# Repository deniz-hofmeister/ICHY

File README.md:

# ICHY - 8-Element Microphone Phased Array

## Project Overview
ICHY is a 8-element microphone phased array designed for high-precision audio source localization and beamforming. This document outlines the key design considerations, components, and implementation approach.

## Key Design Elements

### Hardware
- **Microphones**: 8 MEMS microphones with matched frequency response
- **Geometry**: Square array of 4x4 microphones
- **Spacing**: λ/2 spacing to prevent spatial aliasing at target frequencies
- **ADC**: Simultaneous sampling across all channels

### Signal Processing
- **Beamforming Algorithm**: Delay-and-sum with optional adaptive algorithms
- **Calibration**: Inter-microphone calibration methodology
- **Filtering**: Band-pass filtering to focus on frequencies of interest
- **Direction Finding**: MUSIC or SRP-PHAT algorithm implementation

### Software
- **DSP Pipeline**: Real-time processing chain
- **Visualization**: Direction-of-arrival display
- **Interface**: Configuration and monitoring interface
- **Data Storage**: Recording capabilities for post-processing

### Performance Targets
- **Angular Resolution**: <5° at target frequency range
- **Frequency Range**: 1kHz - 8kHz optimal operation
- **Processing Latency**: <50ms for real-time applications

## Data Acquisition Architecture

### Minimal Hardware Configuration for Jetson Processing

#### Essential Hardware Components
- **Microphones**: 8 digital MEMS microphones (I2S/PDM output)
- **Clock Source**: Single master clock with distribution network to ensure phase alignment
- **Audio Codec/Interface**: Audio interface with multi-channel input capabilities
- **Physical Array Structure**: Precise physical positioning framework for microphones
- **Power Conditioning**: Clean power supply with proper isolation

#### Non-Replaceable Hardware Elements
1. **Microphone Transducers**: Physical conversion of sound to electrical signals cannot be done in software
2. **Clock Synchronization Hardware**: Physical timing alignment between microphones (~1μs precision)
3. **Physical Array Geometry**: Precise spatial positioning that affects beamforming accuracy
4. **Signal Conditioning**: Analog filters and buffers to maintain signal integrity
5. **ADC Hardware**: Conversion from analog to digital (integrated in digital MEMS mics)

### Jetson-Based Processing Approach
- **Direct Interfaces**: Utilize Jetson's I2S/SPI interfaces for direct microphone connection where possible
- **Audio Interface Options**:
  1. Direct connection of PDM microphones to Jetson's hardware interfaces
  2. Multi-channel audio codec with TDM output connected to Jetson
  3. USB audio interface with multi-channel capability

### Software-Replaceable Components
- **Digital Filtering**: All filtering can be performed in software on Jetson
- **Beamforming Algorithms**: Implemented entirely in CUDA on Jetson GPU
- **Signal Conditioning**: Digital gain, normalization in software
- **Channel Synchronization**: Fine synchronization adjustments in software
- **Calibration**: Software-based microphone calibration routines
- **Direction Finding**: All direction finding algorithms in CUDA

### Jetson Processing Implementation
- **Nvidia Jetson Advantages**:
  1. **Integrated Solution**: ARM CPU cores + CUDA-capable GPU on single board
  2. **Direct I/O**: Hardware interfaces for connecting to microphone array
  3. **Unified Memory**: Shared memory architecture for efficient CPU-GPU data exchange
  4. **Complete Software Stack**: CUDA libraries for signal processing optimization
  
- **Jetson Signal Processing Pipeline**:
  1. **Data Acquisition**: 
     - Direct digital sampling from microphones via I2S/PDM interfaces
     - DMA transfer to Jetson memory with minimal CPU involvement
  
  2. **Pre-Processing on CPU**:
     - Initial buffering and sample rate conversion if needed
     - Channel synchronization fine-tuning
     - Data preparation for GPU processing
  
  3. **GPU Processing with CUDA**:
     - Batch processing of multi-channel audio data
     - FFT-based operations across all channels in parallel
     - Beamforming coefficients calculation
     - Direction-of-arrival estimation using MUSIC/SRP-PHAT
  
  4. **Real-time Visualization and Output**:
     - Direction finding results visualization
     - Beamformed audio output
     - Optional raw data storage for post-processing

- **Optimized Jetson Implementation**:
  - Use of Jetson-specific optimizations (cuDNN, TensorRT if applicable)
  - Zero-copy memory operations between CPU and GPU when possible
  - Asynchronous processing to maintain real-time performance
  - GPU kernel fusion to minimize data movement

### Power and Thermal Considerations
- **Power Distribution**: Clean, low-noise power supply to each microphone
- **Isolation**: Digital/analog domain isolation to prevent noise coupling
- **Thermal Design**: Heat dissipation strategy for continuous operation

## Design Artifacts

### PCB Design

### Schematic

### 3D View

### Left side of the PCB, right is mirrored

## Next Steps
- Detailed microphone selection and array geometry calculation
- Electronics design and component selection
- DSP algorithm implementation
- Mechanical design and housing
- Software development and user interface
- Testing and calibration methodology

## References
- Key academic papers and resources for phased array design
- Component datasheets and reference implementations

## Developer Guide
- https://docs.nvidia.com/jetson/archives/r36.4/DeveloperGuide/SD/Communications/AudioSetupAndDevelopment.html

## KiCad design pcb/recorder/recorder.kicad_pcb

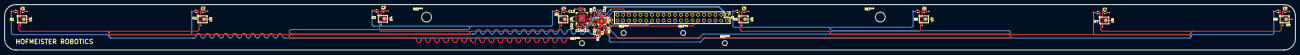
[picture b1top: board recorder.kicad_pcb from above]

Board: 4 copper layers, 569.0 x 20.0 mm, 37 parts (0 on the bottom side), 27 nets.

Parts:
C1, C2, C3, C4, C5, C6, C7, C8, C9, C10, C11: 220nF; C_0603_1608Metric
C12: 1uF; C_0603_1608Metric
C13: 4700nF; C_0603_1608Metric
C14: 10uF; C_0603_1608Metric
J1: GPIO_Conn_02x20_Odd_Even; PinHeader_2x20_P2.54mm_Vertical
R1, R2, R3, R4, R5, R6, R7, R8: 100; R_0603_1608Metric
R9: 10000; R_0603_1608Metric
R12, R13, R14: 22; R_0603_1608Metric
U1, U3, U4, U5, U6, U7, U8, U9: IM73D122V01
U2: ADAU7118; LFCSP-16
U10: TPS7A4700RGWT; RGW0020A-IPC_A

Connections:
/CLK0: R12.2, U1.3 (CLOCK), U3.3 (CLOCK), U4.3 (CLOCK), U5.3 (CLOCK)
/CLK1: R13.2, U6.3 (CLOCK), U7.3 (CLOCK), U8.3 (CLOCK), U9.3 (CLOCK)
/DAT0: R1.2, R2.2, U2.2 (PDM_DAT0)
/DAT1: R3.2, R4.2, U2.3 (PDM_DAT1)
/DAT2: R5.2, R6.2, U2.5 (PDM_DAT2)
/DAT3: R7.2, R8.2, U2.6 (PDM_DAT3)
/DIN: J1.38 (I2S0_DIN), R14.1
/DVDD: C1.1, C2.1, C3.1, C4.1, C5.1, C6.1, C7.1, C8.1, C9.1, C13.1, U1.2 (VDD), U1.4 (LR), U2.14 (DVDD), U3.2 (VDD), U4.2 (VDD), U4.4 (LR), U5.2 (VDD), U6.2 (VDD), U6.4 (LR), U7.2 (VDD), U8.2 (VDD), U8.4 (LR), U9.2 (VDD), U10.1 (OUT), U10.3 (SENSE_FB)
/ENABLE: C11.1, R9.1, U2.13 (EN)
/FS: J1.35 (I2S0_FS), U2.9 (FSYNC)
/IOVDD: C10.1, C14.1, J1.1 (3V3), R9.2, U2.16 (IOVDD), U10.13 (EN), U10.15 (IN)
/SCL: J1.28 (I2C0_SCL), U2.7 (SCL)
/SCLK: J1.12 (I2S0_SCLK), U2.10 (BLCK)
/SDA: J1.27 (I2C0_SDA), U2.8 (SDA)
GND: C1.2, C2.2, C3.2, C4.2, C5.2, C6.2, C7.2, C8.2, C9.2, C10.2, C11.2, C12.2, C13.2, C14.2, J1.6 (GND), U1.5 (GND), U2.12 (ADDR/CONFIG), U2.15 (GND), U2.17 (EPAD), U3.4 (LR), U3.5 (GND), U4.5 (GND), U5.4 (LR), U5.5 (GND), U6.5 (GND), U7.4 (LR), U7.5 (GND), U8.5 (GND), U9.4 (LR), U9.5 (GND), U10.7 (GND), U10.10 (0P4V), U10.21 (Thermal_Pad)
unnamed: R1.1, U1.1 (DATA)
unnamed: R12.1, U2.1 (PDM_CLK0)
unnamed: R13.1, U2.4 (PDM_CLK1)
unnamed: R14.2, U2.11 (SDATA)
unnamed: R2.1, U3.1 (DATA)
unnamed: R3.1, U4.1 (DATA)
unnamed: R4.1, U5.1 (DATA)
unnamed: R5.1, U6.1 (DATA)
unnamed: R6.1, U7.1 (DATA)
unnamed: R7.1, U8.1 (DATA)
unnamed: R8.1, U9.1 (DATA)
unnamed: C12.1, U10.14 (NR)

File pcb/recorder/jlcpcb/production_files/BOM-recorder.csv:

Comment,Designator,Footprint,LCSC,Quantity
1uF,C12,C_0603_1608Metric,C105524,1
220nF,"C1,C10,C11,C2,C3,C4,C5,C6,C7,C8,C9",C_0603_1608Metric,C106250,11
4700nF,C13,C_0603_1608Metric,C107368,1
100,"R1,R2,R3,R4,R5,R6,R7,R8",R_0603_1608Metric,C22775,8
22,"R12,R13,R14",R_0603_1608Metric,C23345,3
10000,R9,R_0603_1608Metric,C25804,1
TPS7A4700RGWT,U10,RGW0020A-IPC_A,C28286,1
10uF,C14,C_0603_1608Metric,C3039698,1
GPIO_Conn_02x20_Odd_Even,,PinHeader_2x20_P2.54mm_Vertical,C5224014,0
IM73D122V01,"U1,U3,U4,U5,U6,U7,U8,U9",IM73D122V01,C5563886,8
ADAU7118,U2,LFCSP-16,C654437,1

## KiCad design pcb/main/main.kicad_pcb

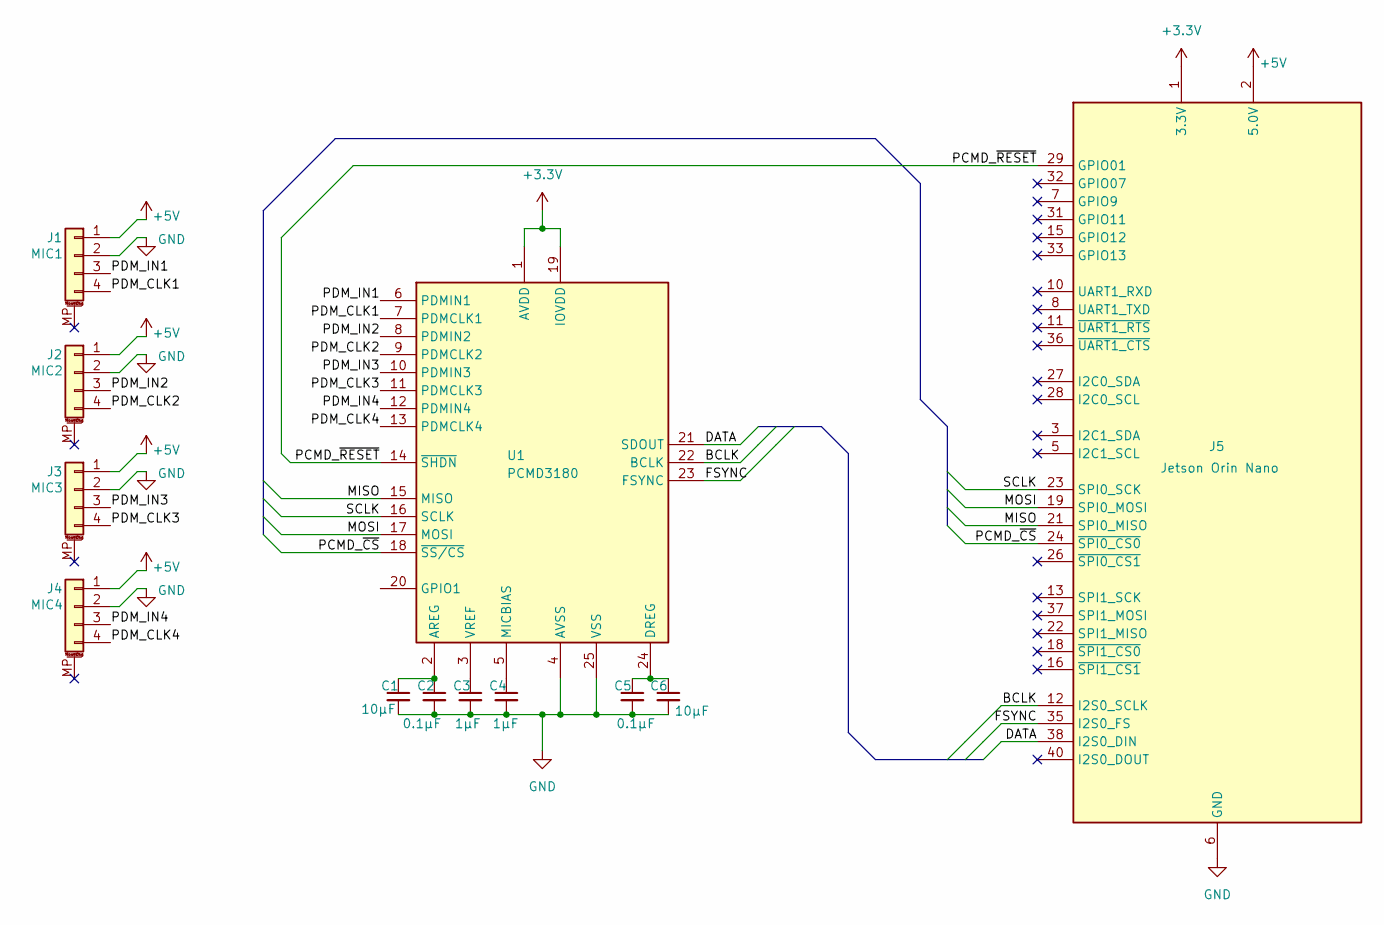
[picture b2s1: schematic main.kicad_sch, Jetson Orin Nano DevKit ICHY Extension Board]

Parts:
C1, C6: 10μF; C_0201_0603Metric
C2, C5: 0.1μF; C_0201_0603Metric
C3, C4: 1μF; C_0201_0603Metric
J1: MIC1; Molex_Pico-Clasp_202396-0407_1x04-1MP_P1.00mm_Horizontal
J2: MIC2; Molex_Pico-Clasp_202396-0407_1x04-1MP_P1.00mm_Horizontal
J3: MIC3; Molex_Pico-Clasp_202396-0407_1x04-1MP_P1.00mm_Horizontal
J4: MIC4; Molex_Pico-Clasp_202396-0407_1x04-1MP_P1.00mm_Horizontal
J5: Jetson Orin Nano; PinSocket_2x20_P2.54mm_Vertical
U1: PCMD3180; Texas_RTW_WQFN-24-1EP_4x4mm_P0.5mm_EP2.7x2.7mm_ThermalVias

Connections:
+3.3V: J5.1 (3.3V), J5.17 (3.3V), U1.1 (AVDD), U1.19 (IOVDD)
+5V: J1.1, J2.1, J3.1, J4.1, J5.2 (5.0V), J5.4 (5.0V)
/BCLK: J5.12 (I2S0_SCLK), U1.22 (BCLK)
/DATA: J5.38 (I2S0_DIN), U1.21 (SDOUT)
/FSYNC: J5.35 (I2S0_FS), U1.23 (FSYNC)
/MISO: J5.21 (SPI0_MISO), U1.15 (MISO)
/MOSI: J5.19 (SPI0_MOSI), U1.17 (MOSI)
/PCMD_~CS: J5.24 (~SPI0_CS0), U1.18 (~SS/CS)
/PCMD_~RESET: J5.29 (GPIO01), U1.14 (~SHDN)
/PDM_CLK1: J1.4, U1.7 (PDMCLK1)
/PDM_CLK2: J2.4, U1.9 (PDMCLK2)
/PDM_CLK3: J3.4, U1.11 (PDMCLK3)
/PDM_CLK4: J4.4, U1.13 (PDMCLK4)
/PDM_IN1: J1.3, U1.6 (PDMIN1)
/PDM_IN2: J2.3, U1.8 (PDMIN2)
/PDM_IN3: J3.3, U1.10 (PDMIN3)
/PDM_IN4: J4.3, U1.12 (PDMIN4)
/SCLK: J5.23 (SPI0_SCK), U1.16 (SCLK)
GND: C1.2, C2.2, C3.2, C4.2, C5.2, C6.2, J1.2, J2.2, J3.2, J4.2, J5.6 (GND), J5.9 (GND), J5.14 (GND), J5.20 (GND), J5.25 (GND), J5.30 (GND), J5.34 (GND), J5.39 (GND), U1.4 (AVSS), U1.25 (VSS)
unnamed: C1.1, C2.1, U1.2 (AREG)
unnamed: C5.1, C6.1, U1.24 (DREG)
unnamed: C4.1, U1.5 (MICBIAS)
unnamed: C3.1, U1.3 (VREF)

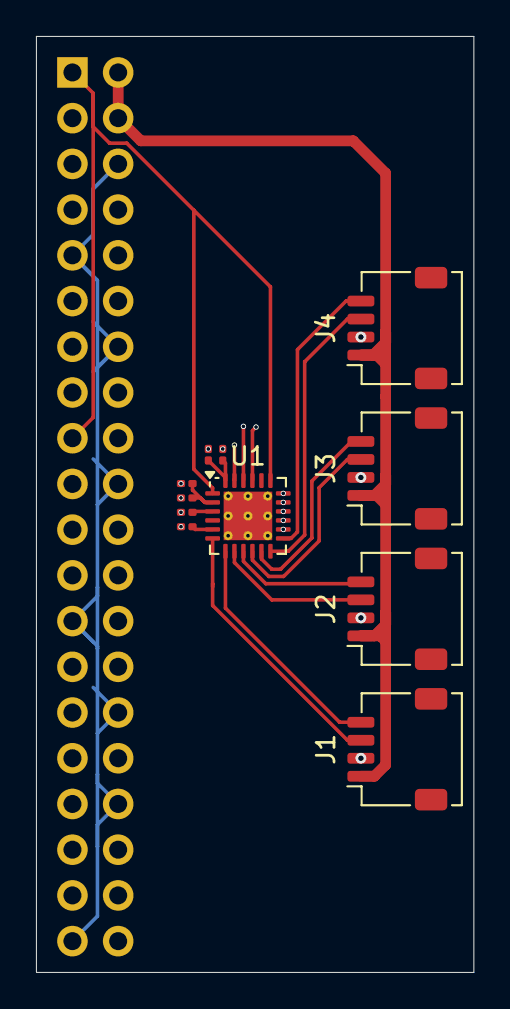
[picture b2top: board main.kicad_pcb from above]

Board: 4 copper layers, 24.3 x 52.0 mm, 12 parts (1 on the bottom side), 23 nets.

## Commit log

2025-04-01 readme
2025-04-02 mic check
2025-04-03 added some specs for TDM conversion
2025-04-10 option 3, and comparison
2025-04-10 added discussion
2025-04-13 Prototype v1 Target
2025-04-19 kicad imports not functional yet
2025-04-22 inter mic distance
2025-04-23 Add initial PCB design.
2025-04-23 Update scaling of molex connector to convert from mm to inch :(
2025-06-21 final changes
2025-06-21 changed design to single-row, no connectors
2025-06-21 images added
2025-06-21 another pcb view
2025-06-21 shrunk pcb
2025-06-21 clock traces redone
2025-06-21 traces redone, DATA and CLK matched
2025-06-21 DRC updates
2025-06-21 shrunk to 569 mm
2025-06-21 v0.2
